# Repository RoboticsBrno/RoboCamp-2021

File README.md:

View this project on [CADLAB.io](https://cadlab.io/project/24548). 

# RoboCamp-2021

Podklady a web k Robotickému táboru 2021. 

K dispozici na [2021.robotickytabor.cz](https://2021.robotickytabor.cz/).

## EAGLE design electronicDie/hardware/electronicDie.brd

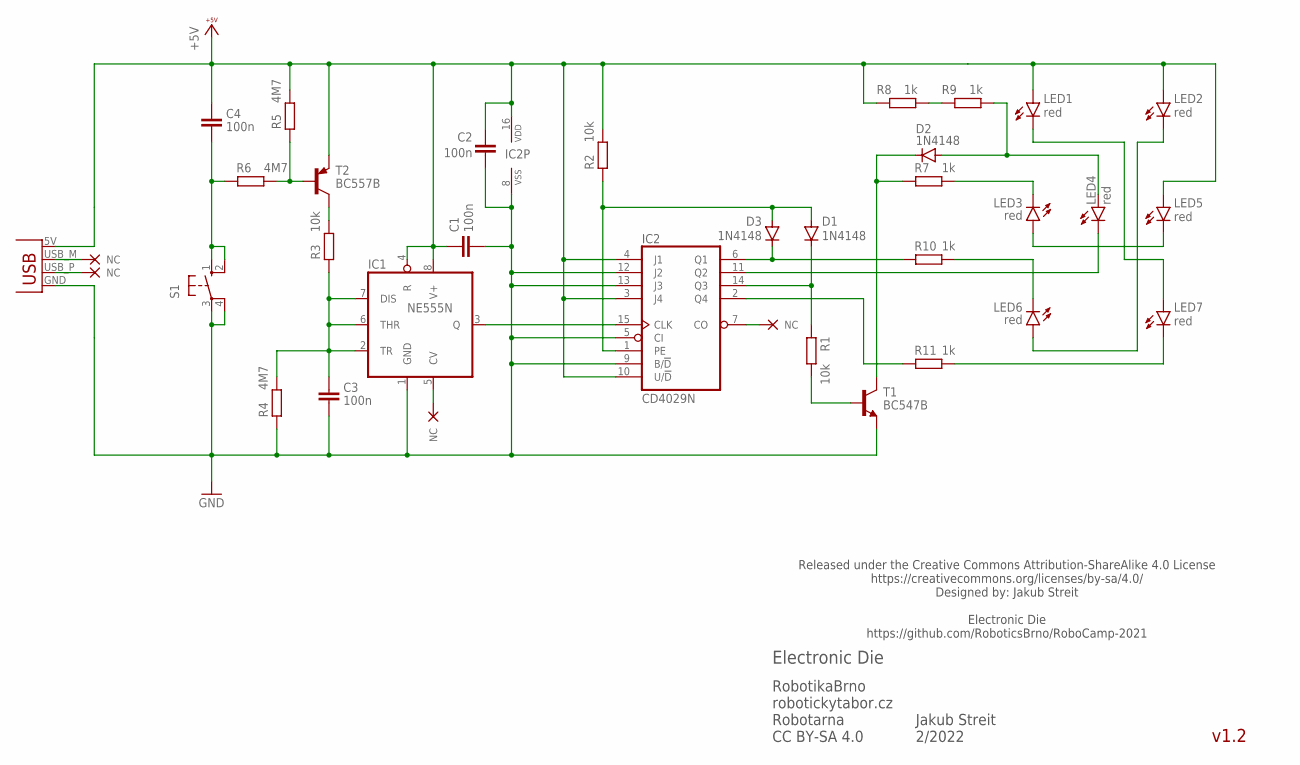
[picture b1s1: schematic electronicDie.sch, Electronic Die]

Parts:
C1, C2, C3, C4: 100n; C050-024X044
D1, D2, D3: 1N4148; DO35-10
IC1: NE555N; DIL08
IC2: CD4029N; DIL16
LED1, LED2, LED3, LED4, LED5, LED6, LED7: red; LED5MM
R1, R2, R3: 10k; 0207/12
R4, R5, R6: 4M7; 0207/12
R7, R8, R9, R10, R11: 1k; 0207/12
S1: 10-XX; B3F-10XX
T1: BC547B; TO92-CBE
T2: BC557B; TO92-CBE
X1: USBPCB; USB-A-PCB

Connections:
+5V: C1.1, C2.1, C4.1, IC1.4 (R), IC1.8 (V+), IC2.3 (J4), IC2.4 (J1), IC2.10 (U/!D), IC2.16 (VDD), LED1.A, LED2.A, LED5.A, R2.2, R5.2, R8.2, T2.E, X1.5V (VBUS)
GND: C1.2, C2.2, C3.2, IC1.1 (GND), IC2.5 (CI), IC2.8 (VSS), IC2.9 (B/!D), IC2.12 (J2), IC2.13 (J3), R4.1, S1.3, S1.4 (P1), T1.E, X1.GND
unnamed: C4.2, R6.1, S1.1 (S), S1.2 (S1)
unnamed: R5.1, R6.2, T2.B
unnamed: R8.1, R9.2
unnamed: R3.2, T2.C
unnamed: C3.1, IC1.2 (TR), IC1.6 (THR), IC1.7 (DIS), R3.1, R4.2
unnamed: IC1.3 (Q), IC2.15 (CLK)
unnamed: LED6.K (C), R10.2
unnamed: D1.A, D3.A, IC2.1 (PE), R2.1
unnamed: D3.C, IC2.6 (Q1), R10.1
unnamed: D1.C, IC2.14 (Q3), R1.1
unnamed: IC2.2 (Q4), R11.1
unnamed: LED3.A, LED5.K (C)
unnamed: LED2.K (C), LED6.A
unnamed: LED1.K (C), LED7.A
unnamed: R1.2, T1.B
unnamed: LED3.K (C), R7.2
unnamed: D2.A, LED4.A, R9.1
unnamed: IC2.11 (Q2), LED4.K (C)
unnamed: D2.C, R7.1, T1.C
unnamed: LED7.K (C), R11.2

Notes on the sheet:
v1.2
RobotikaBrno robotickytabor.cz Robotarna CC BY-SA 4.0
Electronic Die
Released under the Creative Commons Attribution-ShareAlike 4.0 License https://creativecommons.org/licenses/by-sa/4.0/ Designed by: Jakub Streit Electronic Die https://github.com/RoboticsBrno/RoboCamp-2021
Jakub Streit 2/2022

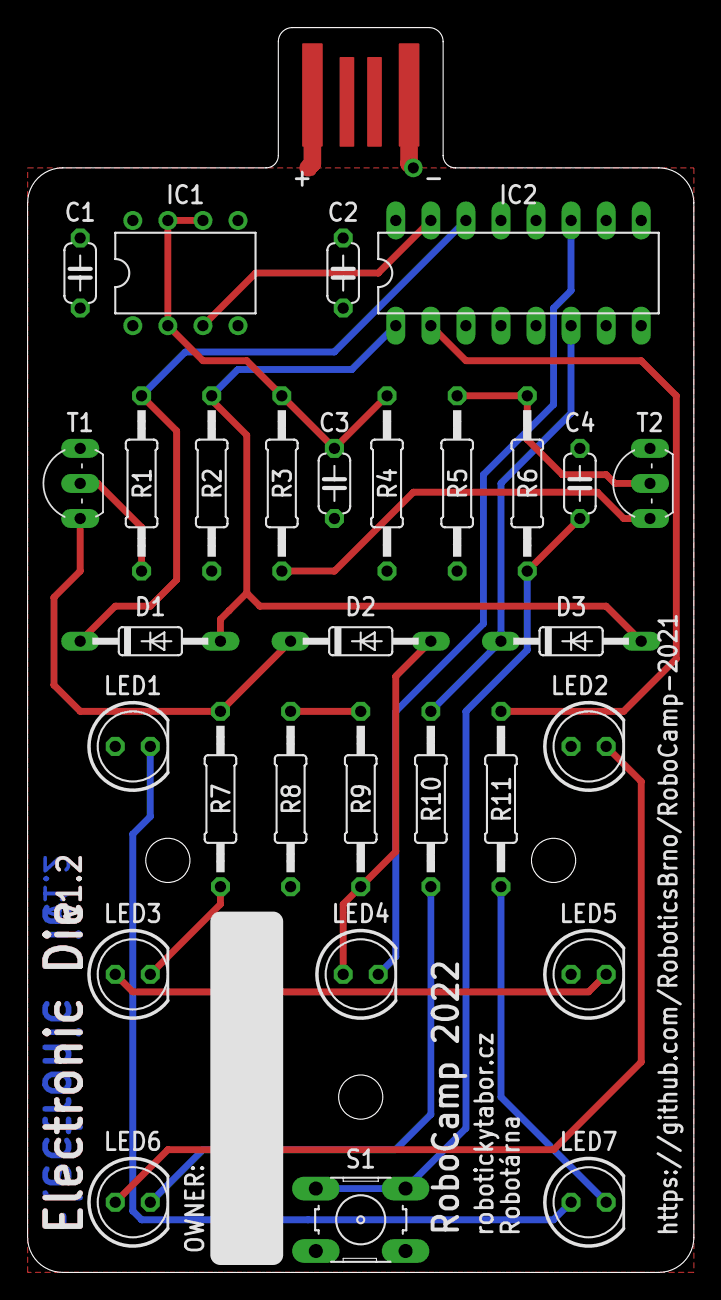
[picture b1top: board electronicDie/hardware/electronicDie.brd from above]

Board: 2 copper layers, 48.3 x 90.2 mm, 31 parts (0 on the bottom side), 22 nets.

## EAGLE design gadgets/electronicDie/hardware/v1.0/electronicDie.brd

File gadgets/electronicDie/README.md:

# O co jde?

Elektronická hrací kostka je jednoduché elektronické zařízení, které vám nahradí klasickou hrací kostku.
Ovládá se jedním tlačítkem na desce, kterým můžete zapnout losování čísla. Jakmile vám jedno číslo padne, bude na kostce svítit až do dalšího hodu.

Tak směle házejte a nebojte se zahrát si spolu třeba kostky.

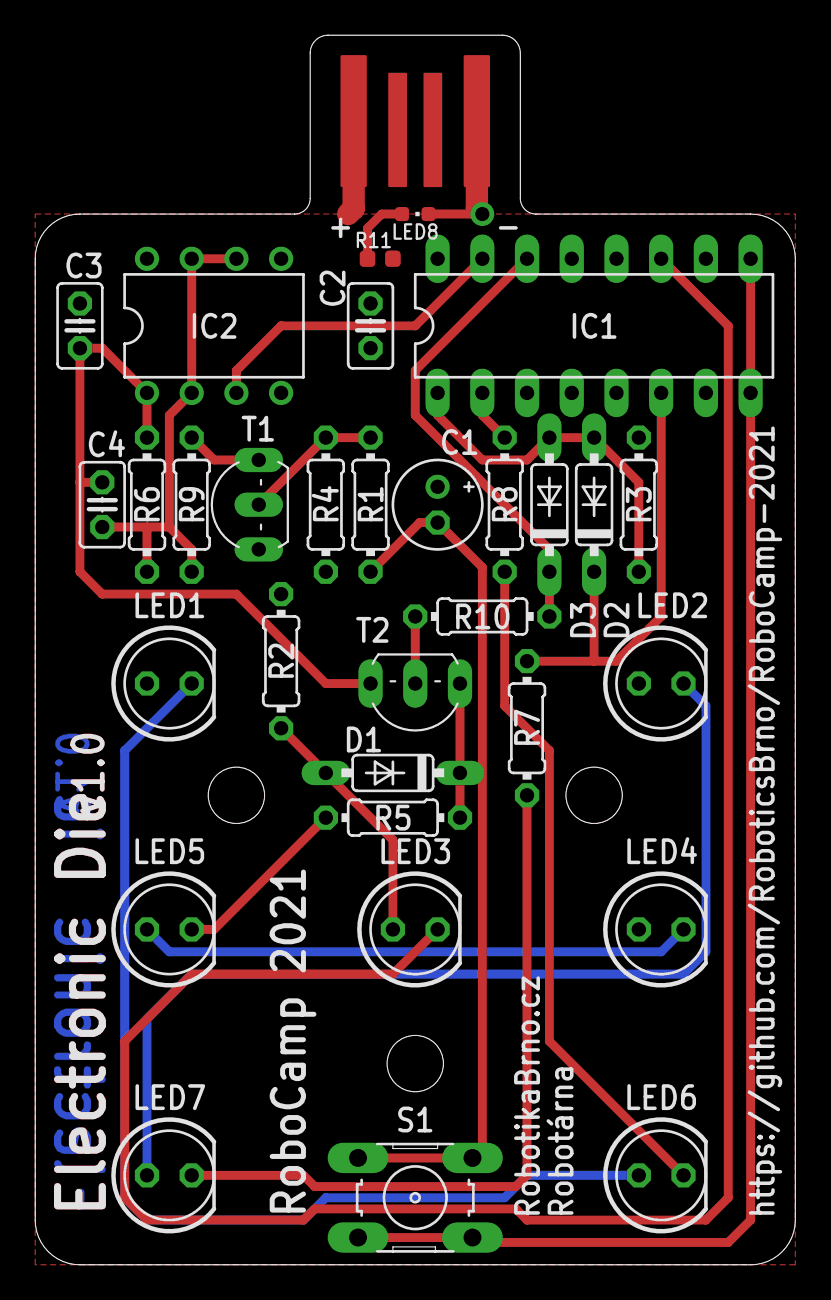
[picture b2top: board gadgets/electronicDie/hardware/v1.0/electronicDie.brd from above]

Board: 2 copper layers, 43.2 x 69.8 mm, 32 parts (0 on the bottom side), 22 nets.

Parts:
C1: 1u; E2-5
C2, C3, C4: 100n; C025-025X050
D1, D2, D3: 1N4148; DO35-7
IC1: CD4029N; DIL16
IC2: NE555N; DIL08
LED1, LED2, LED3, LED4, LED5, LED6, LED7: red; LED5MM
LED8: green; CHIPLED_0603
R1: 3M3; 0204/7
R2: 2k2; 0204/7
R3, R10: 100k; 0204/7
R4: 10M; 0204/7
R5, R7, R8: 1k; 0204/7
R6: 10k; 0204/7
R9: 4M7; 0204/7
R11: 1k; R0603
S1: B3F-10XX
T1: BC327; TO92-EBC
T2: BC337; TO92-CBE
X1: USBPCB; USB-A-PCB

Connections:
+5V: C1.+, C2.1, C3.1, IC1.3, IC1.4, IC1.10, IC1.16, IC2.4, IC2.8, LED1.A, LED2.A, LED4.A, R1.2, R2.2, R3.2, R11.2, T1.E, X1.5V
GND: C2.2, C3.2, C4.2, IC1.5, IC1.8, IC1.9, IC1.12, IC1.13, IC2.1, LED8.C, R9.1, S1.3, S1.4, T2.E, X1.GND
unnamed: C1.-, R4.1, S1.1, S1.2
unnamed: R1.1, R4.2, T1.B
unnamed: LED8.A, R11.1
unnamed: R6.2, T1.C
unnamed: C4.1, IC2.2, IC2.6, IC2.7, R6.1, R9.2
unnamed: IC1.15, IC2.3
unnamed: LED7.K, R7.2
unnamed: D2.A, D3.A, IC1.1, R3.1
unnamed: D2.C, IC1.6, R7.1
unnamed: D3.C, IC1.14, R10.1
unnamed: IC1.2, R8.1
unnamed: LED4.K, LED5.A
unnamed: LED2.K, LED7.A
unnamed: LED1.K, LED6.A
unnamed: R10.2, T2.B
unnamed: LED5.K, R5.2
unnamed: D1.A, LED3.A, R2.1
unnamed: IC1.11, LED3.K
unnamed: D1.C, R5.1, T2.C
unnamed: LED6.K, R8.2

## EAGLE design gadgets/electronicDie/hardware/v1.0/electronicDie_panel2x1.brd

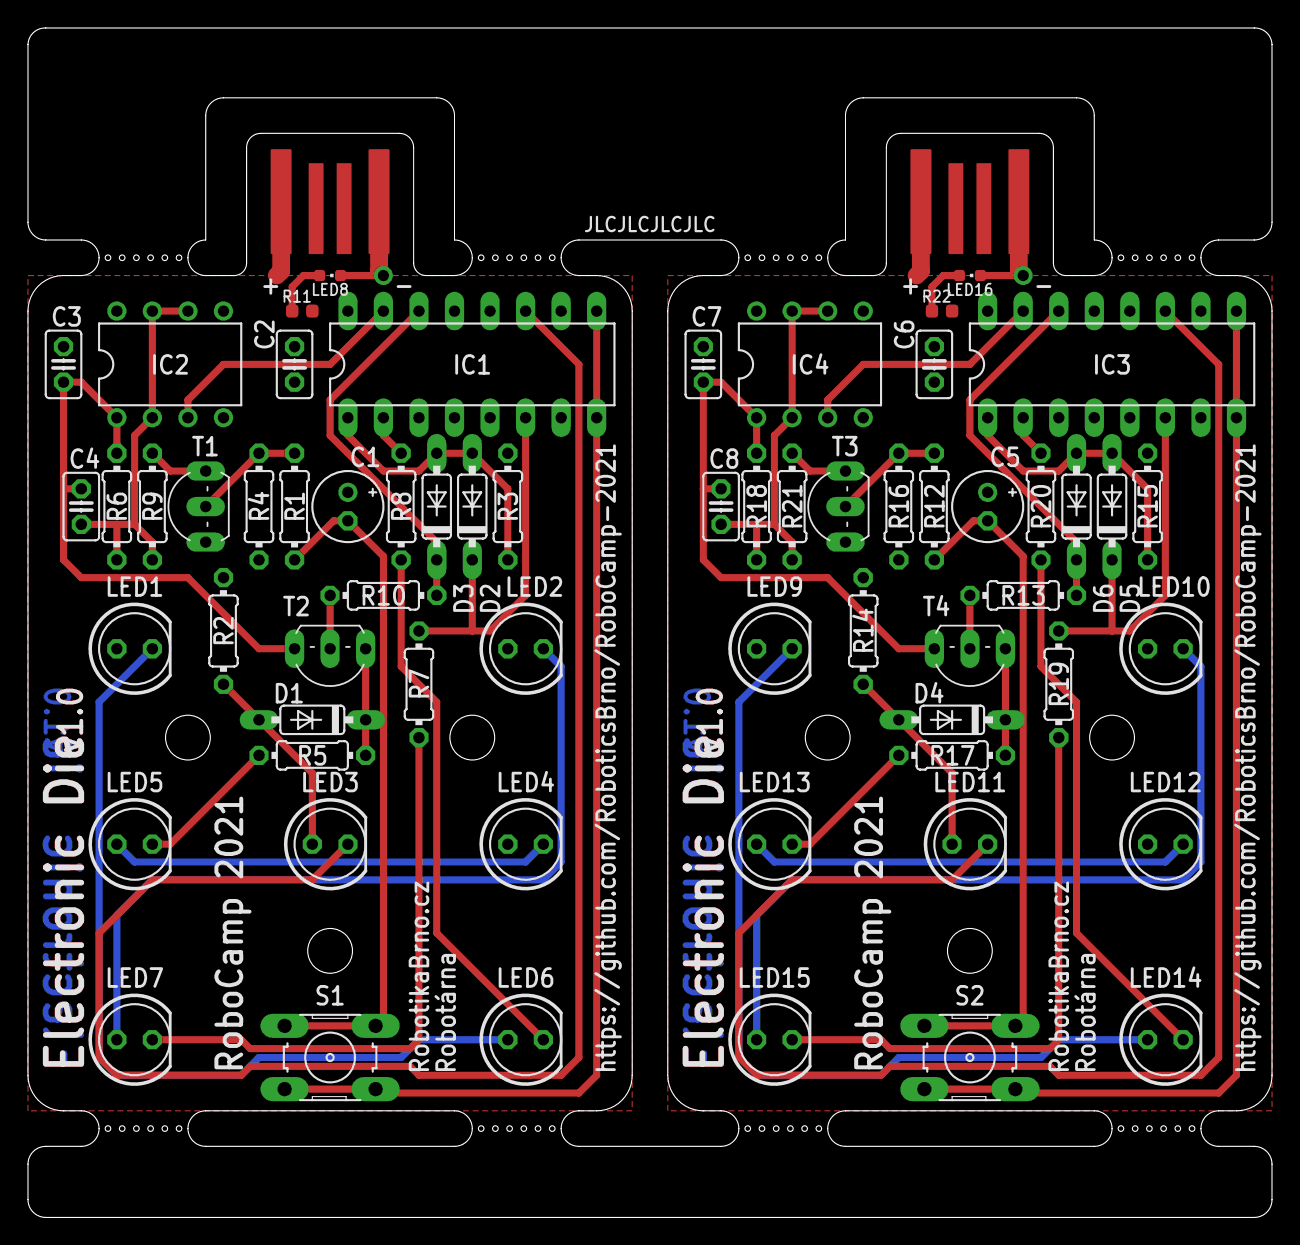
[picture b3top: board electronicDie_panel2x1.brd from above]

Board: 2 copper layers, 88.9 x 85.0 mm, 64 parts (0 on the bottom side), 44 nets.

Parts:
C1, C5: 1u; E2-5
C2, C3, C4, C6, C7, C8: 100n; C025-025X050
D1, D2, D3, D4, D5, D6: 1N4148; DO35-7
IC1, IC3: CD4029N; DIL16
IC2, IC4: NE555N; DIL08
LED1, LED2, LED3, LED4, LED5, LED6, LED7, LED9, LED10, LED11, LED12, LED13, LED14, LED15: red; LED5MM
LED8, LED16: green; CHIPLED_0603
R1, R12: 3M3; 0204/7
R2, R14: 2k2; 0204/7
R3, R10, R13, R15: 100k; 0204/7
R4, R16: 10M; 0204/7
R5, R7, R8, R17, R19, R20: 1k; 0204/7
R6, R18: 10k; 0204/7
R9, R21: 4M7; 0204/7
R11, R22: 1k; R0603
S1, S2: B3F-10XX
T1, T3: BC327; TO92-EBC
T2, T4: BC337; TO92-CBE
X1, X2: USBPCB; USB-A-PCB

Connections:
+5V: C1.+, C2.1, C3.1, IC1.3, IC1.4, IC1.10, IC1.16, IC2.4, IC2.8, LED1.A, LED2.A, LED4.A, R1.2, R2.2, R3.2, R11.2, T1.E, X1.5V
+5V1: C5.+, C6.1, C7.1, IC3.3, IC3.4, IC3.10, IC3.16, IC4.4, IC4.8, LED9.A, LED10.A, LED12.A, R12.2, R14.2, R15.2, R22.2, T3.E, X2.5V
GND: C2.2, C3.2, C4.2, IC1.5, IC1.8, IC1.9, IC1.12, IC1.13, IC2.1, LED8.C, R9.1, S1.3, S1.4, T2.E, X1.GND
GND1: C6.2, C7.2, C8.2, IC3.5, IC3.8, IC3.9, IC3.12, IC3.13, IC4.1, LED16.C, R21.1, S2.3, S2.4, T4.E, X2.GND
unnamed: C1.-, R4.1, S1.1, S1.2
unnamed: R1.1, R4.2, T1.B
unnamed: LED8.A, R11.1
unnamed: R6.2, T1.C
unnamed: C4.1, IC2.2, IC2.6, IC2.7, R6.1, R9.2
unnamed: IC1.15, IC2.3
unnamed: LED7.K, R7.2
unnamed: D2.A, D3.A, IC1.1, R3.1
unnamed: D2.C, IC1.6, R7.1
unnamed: D3.C, IC1.14, R10.1
unnamed: IC1.2, R8.1
unnamed: LED4.K, LED5.A
unnamed: LED2.K, LED7.A
unnamed: LED1.K, LED6.A
unnamed: R10.2, T2.B
unnamed: LED5.K, R5.2
unnamed: D1.A, LED3.A, R2.1
unnamed: IC1.11, LED3.K
unnamed: D1.C, R5.1, T2.C
unnamed: LED6.K, R8.2
unnamed: C5.-, R16.1, S2.1, S2.2
unnamed: R12.1, R16.2, T3.B
unnamed: R18.2, T3.C
unnamed: C8.1, IC4.2, IC4.6, IC4.7, R18.1, R21.2
unnamed: IC3.15, IC4.3
unnamed: D5.A, D6.A, IC3.1, R15.1
unnamed: D5.C, IC3.6, R19.1
unnamed: D6.C, IC3.14, R13.1
unnamed: IC3.2, R20.1
unnamed: LED12.K, LED13.A
unnamed: LED10.K, LED15.A
unnamed: LED15.K, R19.2
unnamed: LED13.K, R17.2
unnamed: D4.A, LED11.A, R14.1
unnamed: IC3.11, LED11.K
unnamed: D4.C, R17.1, T4.C
unnamed: LED9.K, LED14.A
unnamed: R13.2, T4.B
unnamed: LED14.K, R20.2
unnamed: LED16.A, R22.1

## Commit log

2020-12-13 Add template
2021-01-23 Draft first draft of smdChallenge
2021-01-24 Rename smdChallenge to solderingChallenge
2021-01-24 Finish first version of solderingChallenge
2021-02-03 Electronic Die schematic
2021-02-04 Add board
2021-02-04 Add silkscreen
2021-02-05 Add SMD power LED for testing purposes
2021-02-05 Fix +5V polygon
2021-02-05 Add mounting holes
2021-02-05 Set polygons isolation to 12 mils and width to 20 mils
2021-02-05 Add NC symbol to USB data pins
2021-02-05 Add dimensions
2021-02-05 Fix USB width
2021-02-05 Fix silkscreen layer
2021-02-05 Add JLCPCB order number location, fix SMD parts name font size
2021-02-05 Add CAM and DRU configuration
2021-02-05 Electronic Die v1.0
2021-02-11 Add v1.0 BOM (Mouser)
2021-03-22 Add RoboSvit
2021-03-22 Fix typo
2021-05-05 ElectronicDie: fix v1.0 problems - make it bigger - change resistors and diodes package size - make larger spaces between parts - minimize part types - fix PNP transistor pinout - remove SMD power LED
2021-06-03 Add target for gatema gerbers
2021-06-04 ElectronicDie v1.1 gerbers (removed JLCPCB order number label, because of fabrication in Gatema)
2021-06-08 Add USB pads
2021-06-09 Change Helceletka branding
2021-07-03 Remove extra level, add documentation
2021-07-07 Add RoboSvit Doc
2021-07-07 Remove two pictures
2021-07-07 Add CZ and EN manual link
2021-07-08 Add md doc for electron
2021-07-08 Edit schematic images
2021-07-08 Add Logic photo guide
2021-07-08 formulation
2021-07-08 Update electronicDie manual
2021-07-08 Fix electron 1. lesson - resistors
2021-07-08 Add electronicDie manual
2021-07-08 Add Logic text manual
2021-07-08 Minify images, add electronicDie manual
2021-07-08 Update schematic symbols in electron guide
2021-07-09 Add web doc
2021-07-09 Change electron schema color, resize roboSvit
2021-07-09 Add favicon, add logic fancy photos
2021-07-09 Resize electron, solderingCh images
2021-07-09 Fix typo, resize images
2021-07-09 Fix type errors and add whitespace to values
2021-07-09 Fix typos
2021-07-09 Last minute touches
2021-07-09 Empty commit
2021-07-09 Add BlackBox
2021-07-09 Fix more typos
2021-07-09 Fix typos in BlackBox
2021-07-09 Add BlackBox PDF guide
2021-07-09 add PCB of Logic
2021-07-09 Add fancy features
2021-07-09 Add note about polarity
2021-07-09 Add fancy design to index page
2021-07-09 Fix name mistake
2021-07-09 Add electron photos
2021-07-09 Add more fancy photos
2021-07-09 Add SMD fancy photo
2021-07-10 Add logo moustache
2021-07-11 Scale down ridiculously large images
2021-07-11 Move logic code example
2021-07-11 Fix resistor value
2021-07-11 fix mistake in electron guide
2021-07-11 Fix electron image
2021-07-12 Add better image to logic
2021-07-12 Add code documentation
2021-07-13 Add code examples
2021-07-13 Fix buttons Enter
2021-07-14 Add L5 for soldering challenge
2021-07-14 Add links
2021-07-15 Add projects page
2021-07-15 Add CNAME
2021-07-15 Add requirements.txt
2021-07-15 Add note about code examples
2021-07-15 Add IDE install instructions
2021-07-16 Add more projects
2021-07-21 Add links to examples
2021-07-23 Fix site name and url in `mkdocs.yml`
2021-07-23 README: add basic info and link to web
2021-07-23 Backlink to CADLAB.io has been added.
2022-02-01 ElectronicDie v1.2: more resistant to assembly errors - resistors with same value grouped together - diodes grouped together - larger spaces between parts - 2k2 resistor replaced with 2 × 1k (so only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
2022-03-07 Add L0 to soldering challenge
2022-03-17 ElectronicDie v1.2: Add logos, freeze version and add gerbers
2022-07-07 Fix USB size on L0
2022-07-14 Update to newer version, add link to doc, fix 404
2022-07-18 Rotate capacitor on L0
2023-06-30 Add new packages, team
2024-03-01 Deployed 5e6599f with MkDocs version: 1.4.3
2025-02-23 Enhance README with modal for version update and improve content layout
2025-02-23 Update README to include link for new version and adjust modal buttons
2025-03-01 Deployed 798b591 with MkDocs version: 1.4.3

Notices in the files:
parts and their libraries:
diode: Creative Commons Attribution-ShareAlike 4.0 International
